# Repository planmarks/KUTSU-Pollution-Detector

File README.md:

<div align="center">

# KUTSU Sense

**Open environmental monitoring for the air you breathe.**

*CO₂ · VOC · NOx · combustible gas & smoke · temperature · humidity*

</div>

---

## What is KUTSU?

KUTSU is an environmental monitoring and awareness device. It watches indoor air for the
things you can't see or smell, shows the readings on a small OLED display, and **warns you
the moment conditions turn unhealthy** with an on-screen alarm, a buzzer and status LEDs.
Every reading is logged to a MicroSD card, and newer builds can stream data to a phone app or
feed a self-hosted dashboard (the KUTSU Hub) on a Raspberry Pi or spare PC. There's no cloud and no subscription.

KUTSU comes in three configurations:

| Configuration | For whom | Highlights |
|---|---|---|
| 🛠️ **Development platform** | Makers, researchers, civic & environmental projects | All buses and power broken out, fully open firmware |
| ✋ **Handheld** | On-site, walk-up spot checks | LiPo battery, compact, display-led UI, laser pointer |
| 🏠 **Stationary** | Long-term monitoring of rooms and large sites | 5 V powered, MQ-2 gas/smoke sensor, 5 V fan, Wi-Fi dashboard + multi-node mesh |

---

### Where to start

| I want to… | Go to |
|---|---|
| Understand or build the **current device** | [KUTSU 1.0](KUTSU%201.0/README.md) |
| Build a **handheld** from breakout modules | [KUTSU DIY → Handheld](KUTSU%20DIY/KUTSU%20Handheld/README.md) |
| Run the **site dashboard** for stationary units (Raspberry Pi / PC) | [KUTSU Hub](KUTSU%201.0/KutsuHub/README.md) |
| Build a **stationary node** from breakout modules (legacy) | [KUTSU DIY → Stationary](KUTSU%20DIY/KUTSU%20Stationary/README.md) |
| Hack on the original **CircuitPython** prototype | [KUTSU PICO](KUTSU%20PICO/README.md) |
| Read the **JSON data format** (Wi-Fi / SD) | [KUTSU 1.0 DATA_CONTRACT.md](KUTSU%201.0/KutsuFirmwareXIAOESP32Series/DATA_CONTRACT.md) (v4) · [Stationary](KUTSU%20DIY/KUTSU%20Stationary/Firmware/KutsuSense/DATA_CONTRACT.md) (v2) |

---

## Generations at a glance

| | **KUTSU PICO** | **KUTSU DIY — Handheld** | **KUTSU DIY — Stationary** | **KUTSU 1.0** |
|---|---|---|---|---|
| **Status** | Original prototype | Legacy, available | Legacy, available | ✅ **Current** |
| **MCU** | Pimoroni Pico LiPo (RP2040) | Seeed XIAO ESP32-C3 / C5 | Espressif ESP32-C5-DevKitC-1 v1.2 | Seeed XIAO ESP32-C6 / C5 / C3 / S3 |
| **Firmware** | CircuitPython 10.x | Arduino / C++ | Arduino / C++ | Arduino / C++ |
| **CO₂** | CCS811 (estimated eCO₂) | CCS811 (estimated eCO₂) | CCS811 (estimated eCO₂) | **SCD41 (true NDIR CO₂)**, CCS811 if fitted |
| **VOC** | SGP40 index · CCS811 TVOC | CCS811 TVOC | CCS811 TVOC | **SGP41 VOC index** |
| **NOx** | — | — | — | **SGP41 NOx index** |
| **Temp / RH** | HTU21D | HTU21D | HTU21D | **SHT40**, HTU21D if fitted |
| **Gas / smoke** | MQ-2 (raw) | — (5 V part, no budget) | MQ-2 (raw) | MQ-2 header (optional, raw) |
| **Feedback** | OLED · buzzer (SOS) | OLED · buzzer | OLED · buzzer · 3 LEDs | OLED · buzzer · warning LED |
| **Logging** | CSV → SD / flash | CSV → SD / flash | **JSON Lines** → SD / flash | **JSON Lines** → SD / flash |
| **Connectivity** | — | Passive Wi-Fi/BLE scanner | **BLE app link + Wi-Fi mesh dashboard** | Passive Wi-Fi/BLE scanner · BLE app link · **KUTSU Hub** (LAN dashboard on a Pi / PC) |
| **Extras** | NFC health tag | NFC health tag | NFC health tag | Laser marker · LiPo · power switch |

---

## How it works (all generations)

Every KUTSU build shares the same core design:

```text
            ┌──────────── once per second ────────────┐
 sensors ──▶ readSensors ─▶ history ─▶ evaluate ─▶ display / alarm ─▶ log row
            └──────────────────────────────────────────┘
                 buttons · buzzer · LEDs · radios run continuously in between
```

- **Sensing loop at 1 Hz.** Each sensor is read into a `Reading` struct. A missing or failed
  sensor is marked *invalid* and is never reported as a fake `0`.
- **Three severities.** Each metric is graded *good* / *warning* `!` / *alert* `!!`. Thresholds
  live in a single config file (`config.h` or `config.py`).
- **Alerts.** An alert brings up a pulsing full-screen warning (5 s on, 1 s gap) and a short
  buzzer pattern, plus LEDs where fitted. Press the screen button to dismiss it. It re-arms
  once the air recovers.
- **History.** The firmware keeps 60 one-minute averages per metric for the on-device
  one-hour charts.
- **Logging.** Data goes to the MicroSD card when one is present and falls back to internal
  flash otherwise. There is no RTC, so timestamps are uptime seconds until a phone or NTP
  supplies the time.

---

## Lineage

1. **KUTSU PICO.** The first prototype was a CircuitPython build on a Raspberry Pi Pico LiPo
   wired to Adafruit-style breakout modules.
2. **Move to ESP32.** CircuitPython does not support the ESP32-C5, so the firmware was
   rewritten in **Arduino/C++**. It then split into a **Handheld** build (XIAO, battery) and a
   **Stationary** build (DevKitC, 5 V, mesh dashboard).
3. **KUTSU 1.0.** The two branches merged onto **one board** and **one firmware**. It runs on
   any footprint-compatible XIAO (ESP32-C6, C5, C3 or S3). The sensors moved from CCS811 +
   HTU21D to the **Sensirion SCD41 / SGP41 / SHT40** stack, so CO₂ is now measured rather than
   estimated. The firmware detects what's fitted, so the old breakouts still work. Stationary
   units feed the KUTSU Hub, a dashboard and collector on a Raspberry Pi or PC.

---

## Roadmap

- [x] Sensirion SCD41 / SGP41 / SHT40 driver migration (KUTSU 1.0)
- [x] BLE app link + Wi-Fi mesh dashboard + JSON data contract (Stationary DIY build)
- [x] Port the JSON data contract to the KUTSU 1.0 firmware (XIAO C3/C5/C6/S3)
- [x] KUTSU Hub: LAN collector + dashboard (Raspberry Pi / Windows) for stationary units
- [x] NTP time source when on Wi-Fi (KUTSU 1.0)
- [ ] BLE app link on KUTSU 1.0 + companion app (React Native / Expo)
- [ ] On-site calibration of CO₂, VOC, NOx and MQ-2 thresholds

---

## ⚠️ Safety notice

KUTSU is an air-quality **awareness and monitoring** instrument. The MQ-2 reports a *relative*
combustible-gas and smoke level. **Do not rely on KUTSU as a certified smoke, carbon-monoxide
or life-safety alarm**, and never use it as the only safety device in a life-safety
application. For regulatory or safety-critical use, validate readings against reference
instruments on site.

---

## License

KUTSU Sense is released under the **[Apache License 2.0](LICENSE)**. This covers the firmware,
documentation and hardware design files (KiCad sources, Gerbers, 3D models). Third-party
libraries bundled in `KUTSU PICO/lib/` keep their own licenses.

---

<div align="center">

*KUTSU — "6th Sense" · By Papathought*

</div>

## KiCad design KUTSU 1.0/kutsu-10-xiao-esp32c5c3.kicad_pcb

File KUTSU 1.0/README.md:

# KUTSU 1.0

> **One board, every use case.** KUTSU 1.0 merges the earlier Handheld and Stationary
> prototypes into a single PCB: the **Kutsu 1 board (rev 3)**. It's built around a Seeed XIAO
> ESP32 module (**C3, C5, C6 or S3**, same footprint, one firmware) and a
> laboratory-calibrated Sensirion sensor stack.

[← Back to project overview](../README.md)

---

## 📚 Documentation

| Document | What's inside |
|---|---|
| **[HARDWARE.md](HARDWARE.md)** | Board overview, bill of materials, pin map, power, design files, fabrication |
| **[Firmware README](KutsuFirmwareXIAOESP32Series/README.md)** | Arduino IDE setup per XIAO module, libraries, wiring, stationary mode + hub, bring-up checklist |
| **[KUTSU Hub](KutsuHub/README.md)** | The LAN dashboard + data collector for stationary units. Runs on a Raspberry Pi or an old Windows PC |
| **[FIRMWARE.md](KutsuFirmwareXIAOESP32Series/FIRMWARE.md)** | Firmware internals: sensor detection, tasks, Wi-Fi state machine, UI, logging, known issues |
| **[DATA_CONTRACT.md](KutsuFirmwareXIAOESP32Series/DATA_CONTRACT.md)** | JSON-Lines record format used by the log, BLE and the KUTSU Hub |
| **[Kutsu Setup app](KutsuSetupApp/)** | Local desktop app to set up a device's WiFi over **Bluetooth or USB** — no nRF Connect needed |
| **[PROVISIONING.md](PROVISIONING.md)** | The BLE GATT + USB-serial setup contract the app and firmware share |
| [kutsu-project.md](kutsu-project.md) | Short product description |

---

## What it measures

| Reading | Sensor | Type | Units |
|---|---|---|---|
| **CO₂** | Sensirion **SCD41** | Photoacoustic NDIR (true CO₂) | ppm |
| **VOC index** | Sensirion **SGP41** | MOx gas sensor + Gas Index Algorithm | 1–500 |
| **NOx index** | Sensirion **SGP41** | MOx gas sensor + Gas Index Algorithm | 1–500 |
| **Temperature** | Sensirion **SHT40** | Digital T/RH | °C |
| **Humidity** | Sensirion **SHT40** | Digital T/RH | %RH |
| **Combustible gas / smoke** | **MQ-2** *(optional, external module)* | Analog MOx | relative |

The firmware **detects its sensors at boot** with an I²C scan, then shows and logs only what it
finds. The original DIY breakouts still work on the same firmware: **CCS811** (eCO₂ + TVOC) and
**HTU21D** (temp/RH). So does a plug-in **SSD1306 OLED module** in place of the on-board panel.

**Why the upgrade matters:** the earlier builds used a CCS811, which *estimates* CO₂ from VOCs.
The SCD41 **measures** CO₂ directly. The SGP41 adds separate **VOC and NOx** indices, which
give a much richer picture than a single "air quality" number.

---

## The three configurations

All three use the **same Kutsu 1 board**. What changes is which parts are fitted, how the
board is powered, and which firmware features are enabled.

| Configuration | Power | Distinctive parts | Networking |
|---|---|---|---|
| 🛠️ **Development platform** | USB-C 5 V | I²C, SD, MQ-2 and power broken out to pads | Open firmware, full access |
| ✋ **Handheld** | LiPo battery (USB-C charging) | Compact, display-led UI, laser marker, small fan | Stays off Wi-Fi. Data via SD card, BLE app or USB |
| 🏠 **Stationary** | 5 V mains / USB | Optional **MQ-2** module, **5 V fan** | Joins Wi-Fi and feeds the **[KUTSU Hub](KutsuHub/README.md)** dashboard on a Pi / PC |

One design to manufacture, one firmware codebase and one data format: a handheld unit and a
wall-mounted site unit speak the same language.

**Handheld vs. stationary is now a software mode**, not just a hardware build — switch it from
the [Kutsu Setup app](KutsuSetupApp/) (Bluetooth/USB), the mobile app or the serial console,
and it persists. In **handheld** mode the unit works stand-alone and stays off Wi-Fi. In
**stationary** mode it joins Wi-Fi, finds the **[KUTSU Hub](KutsuHub/README.md)** (a small app
on a Raspberry Pi or PC on the same network) and streams its readings and log there. The hub
keeps the history and serves the site dashboard. A fresh device boots in handheld mode. See
[PROVISIONING.md](PROVISIONING.md) for the full behavior model and the settings
(buzzer / LED / display / scanning / mode) a connected client can change.

---

## Quick start

1. Install the **esp32 by Espressif** core (≥ 3.3) and select your module: **XIAO_ESP32C3**,
   **XIAO_ESP32C5**, **XIAO_ESP32C6** or **XIAO_ESP32S3**.
2. On C3/C5/C6, set **Partition Scheme → Huge APP (3MB No OTA/1MB SPIFFS)**. Leave **USB CDC On
   Boot → Enabled** (the default); see the
   [firmware README](KutsuFirmwareXIAOESP32Series/README.md#1-board-setup-arduino-ide).
3. Install the libraries listed in the [firmware README](KutsuFirmwareXIAOESP32Series/README.md#2-libraries).
4. Open `KutsuFirmwareXIAOESP32Series/KutsuSense/KutsuSense.ino` and upload.
5. Open the Serial Monitor at **115200**. The I²C scan should list `0x3C 0x44 0x59 0x62`.
6. *(Optional, stationary use)* Start the **[KUTSU Hub](KutsuHub/README.md)** on a Pi or PC
   (`python3 kutsu_hub.py`). Then set the unit to **stationary** with Wi-Fi credentials, using
   the **[Kutsu Setup app](KutsuSetupApp/)** or the Serial Monitor (`mode stationary`,
   `ssid <network>`, `pass <password>`, `connect`). The unit finds the hub by itself. Open the
   address shown on the unit's **Hub** screen.

---

## On-device experience

- **Boot.** A splash screen ("KUTSU / 6th Sense / By Papathought") is followed by a self-test
  screen that shows OK/FAIL for each module.
- **Screens.** One button cycles through **Live → Stats (1-hour sparklines) → Wi-Fi networks →
  BLE devices → Hub** (hub address, sync state, Wi-Fi).
- **Alerts:**

  | Channel | Behaviour |
  |---|---|
  | 🖥️ Display | Full-screen WARNING that pulses (5 s on / 1 s gap) until you dismiss it |
  | 🔊 Buzzer | 3 short beeps once per alert; re-arms after the air recovers |
  | 💡 Warning LED | Solid on alert, slow blink on warning, off when clear |

- **Logging.** JSON Lines go to MicroSD (`/kutsu_log.jsonl`), with internal flash as the
  fallback. Format: [DATA_CONTRACT.md](KutsuFirmwareXIAOESP32Series/DATA_CONTRACT.md).
- **KUTSU Hub.** In stationary mode the unit streams to the hub on the LAN, which charts
  every unit's history, raises alerts and exports CSV.
- **Laser marker.** A hardware switch lights a laser so you can point at the spot you're sampling.

### Default thresholds

| Metric | Warning `!` | Alert `!!` |
|---|---|---|
| CO₂ (SCD41) | ≥ 1000 ppm | ≥ 2000 ppm |
| eCO₂ / TVOC (CCS811 breakout) | ≥ 900 ppm / ≥ 660 ppb | ≥ 2000 ppm / ≥ 3000 ppb |
| VOC index | ≥ 250 | ≥ 400 |
| NOx index | ≥ 20 | ≥ 150 |
| Temperature | 50–60 °C | < 0 °C or > 60 °C |
| Humidity | 25–30 % or 60–70 %RH | < 25 % or > 70 %RH |

> [!NOTE]
> The CO₂, VOC and NOx limits are **provisional**. Calibrate them on site. You can change any
> of them in `config.h`.

---

## Directory contents

| Path | Contents |
|---|---|
| `kutsu-10-xiao-esp32c5c3.kicad_pro` / `.kicad_sch` / `.kicad_pcb` | KiCad project: **Kutsu 1, rev 3** |
| `kutsu-10-xiao-esp32c5c6.net` | Exported netlist *(older, rev 2; see [HARDWARE.md](HARDWARE.md#design-files))* |
| `KUTSUV1 Gerber/` + `KUTSUV1 Gerber.zip` | Fabrication gerbers + drill files |
| `3D/` | PCB render, board models (`.stl`, `.glb`) |
| `Case/` | Enclosure model (`Kutsu 1 Case.blend`) + render |
| `Kutsu Handheld 3D Model.blend` | Industrial-design model |
| `KutsuFirmwareXIAOESP32Series/` | Firmware for this board (XIAO ESP32-C3 / C5 / C6 / S3) |
| `KutsuHub/` | KUTSU Hub: LAN collector + dashboard for stationary units (Python, Raspberry Pi / Windows) |
| `BOM/` | Bill of materials / compliance sheet + component datasheets |
| `*.kicad_prl`, `fp-info-cache`, `.history/` | KiCad local/editor state, not part of the design |

---

## Other hardware variants

The XIAO footprint is pin-identical across the C3, C5, C6 and S3, and this board's firmware
supports all four. The earlier boards and their firmware are still available:

| Variant | MCU | Sensors | Where |
|---|---|---|---|
| **KUTSU 1.0** *(this)* | XIAO ESP32-C3 / C5 / C6 / S3 | SCD41 · SGP41 · SHT40 (+ CCS811 · HTU21D · MQ-2 if fitted) | [`KutsuFirmwareXIAOESP32Series`](KutsuFirmwareXIAOESP32Series/) |
| DIY Handheld | XIAO ESP32-C3 / C5 | CCS811 · HTU21D · | [`KUTSU DIY/KUTSU Handheld`](../KUTSU%20DIY/KUTSU%20Handheld/README.md) |
| DIY Stationary | ESP32-C5-DevKitC-1 | CCS811 · HTU21D · MQ-2 · 3 LEDs | [`KUTSU DIY/KUTSU Stationary`](../KUTSU%20DIY/KUTSU%20Stationary/README.md) |

---

## Roadmap

- [x] Sensirion SCD41 / SGP41 / SHT40 driver migration
- [x] One firmware for XIAO ESP32-C3 / C5 / C6 / S3
- [x] Boot-time I²C detection: on-board Sensirion stack, DIY CCS811/HTU21D breakouts, OLED panel or module
- [x] JSON data contract, ported from the
      [Stationary firmware](../KUTSU%20DIY/KUTSU%20Stationary/Firmware/KutsuSense/README.md)
- [x] **[KUTSU Hub](KutsuHub/README.md)**: LAN collector + dashboard on a Raspberry Pi / PC. It
      replaces the ESP32-hosted dashboard and mesh election, with gap-free history after outages
- [ ] Hub → device settings (thresholds, names) from the dashboard
- [x] NTP time sync when online
- [x] BLE GATT provisioning service + **[Kutsu Setup app](KutsuSetupApp/)** (Bluetooth **or** USB
      WiFi setup from the desktop) — see [PROVISIONING.md](PROVISIONING.md)
- [ ] Hardware bring-up of the merged firmware on each XIAO module (incl. BLE server+scanner coexistence)
- [ ] Package Kutsu Setup as an installable Tauri/Electron app; add firmware info/OTA, FRC calibration, node naming
- [ ] Mobile companion app (React Native / Expo) on the same GATT contract
- [ ] SCD41 fresh-air forced-recalibration (FRC) workflow; on-site threshold tuning
- [ ] BLE bonding / pairing PIN before deploying where open provisioning isn't acceptable

---

## For industrial & site deployment

- **Calibrated measurements.** True CO₂ (NDIR), VOC and NOx indices, temperature and humidity
  come from Sensirion sensors, not estimated proxies.
- **Standalone or fleet.** Each node works on its own: display, LED, alarm and SD log. Put
  several on one Wi-Fi network with the KUTSU Hub running on a Raspberry Pi or spare PC, and
  you get a live site dashboard with full history. There's no cloud and nothing to install
  beyond Python.
- **Your data stays yours.** Logs go to a removable MicroSD card in an open format. There's no
  cloud, no account and no per-seat fee.
- **Resilient.** Every node logs locally whatever the network state, and a failed sensor is
  marked invalid rather than reported as zero.
- **Flexible power.** Run it from 5 V mains with an active fan for permanent installs, or from a
  battery for portable audits.

> [!WARNING]
> KUTSU is an air-quality **awareness** instrument. The MQ-2 reports a *relative* gas/smoke
> level. Do not rely on it as a certified smoke, CO or life-safety alarm.

---

*By Papathought.*

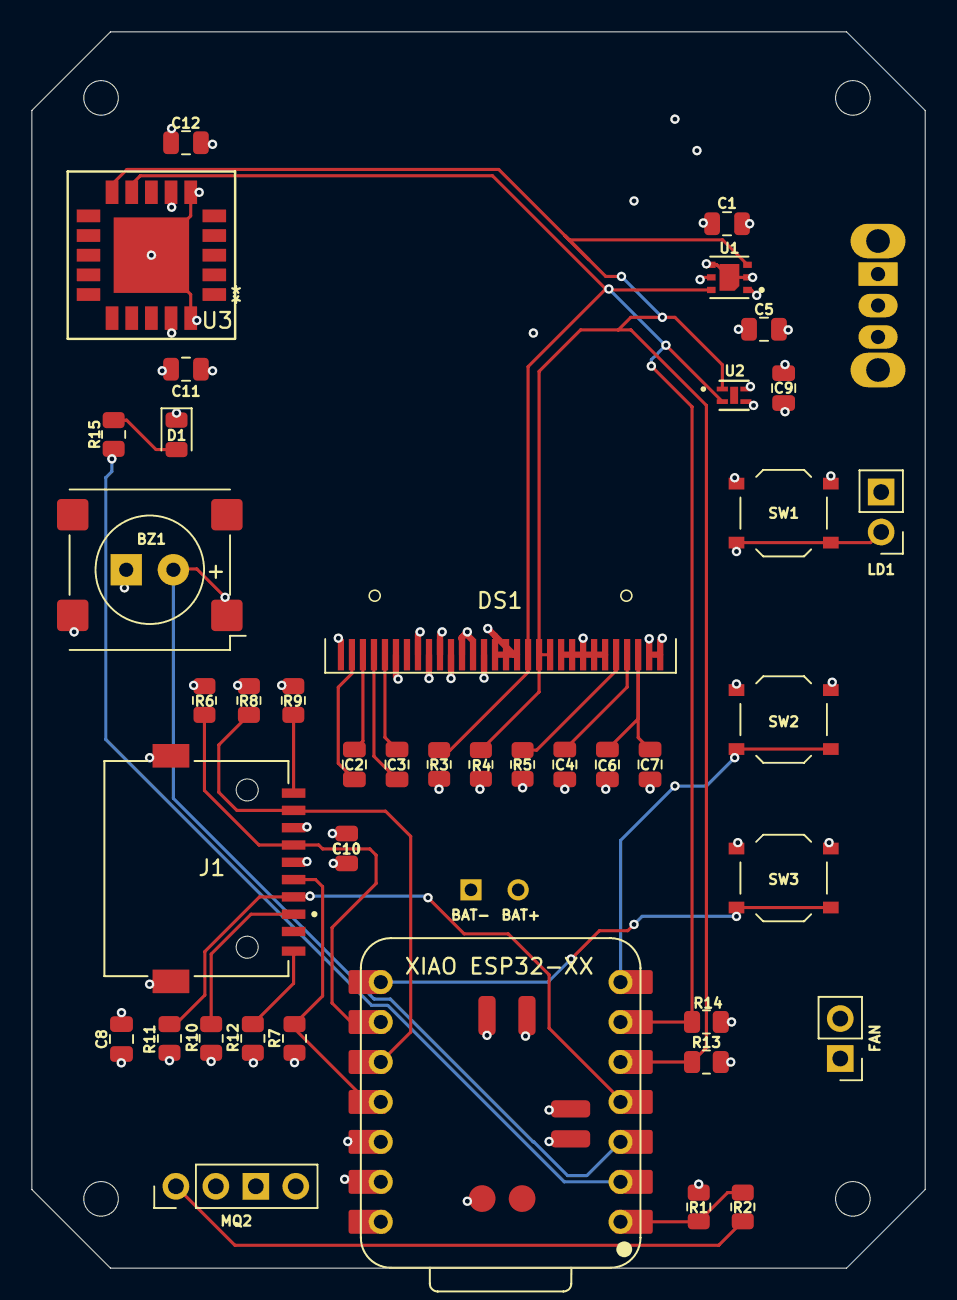
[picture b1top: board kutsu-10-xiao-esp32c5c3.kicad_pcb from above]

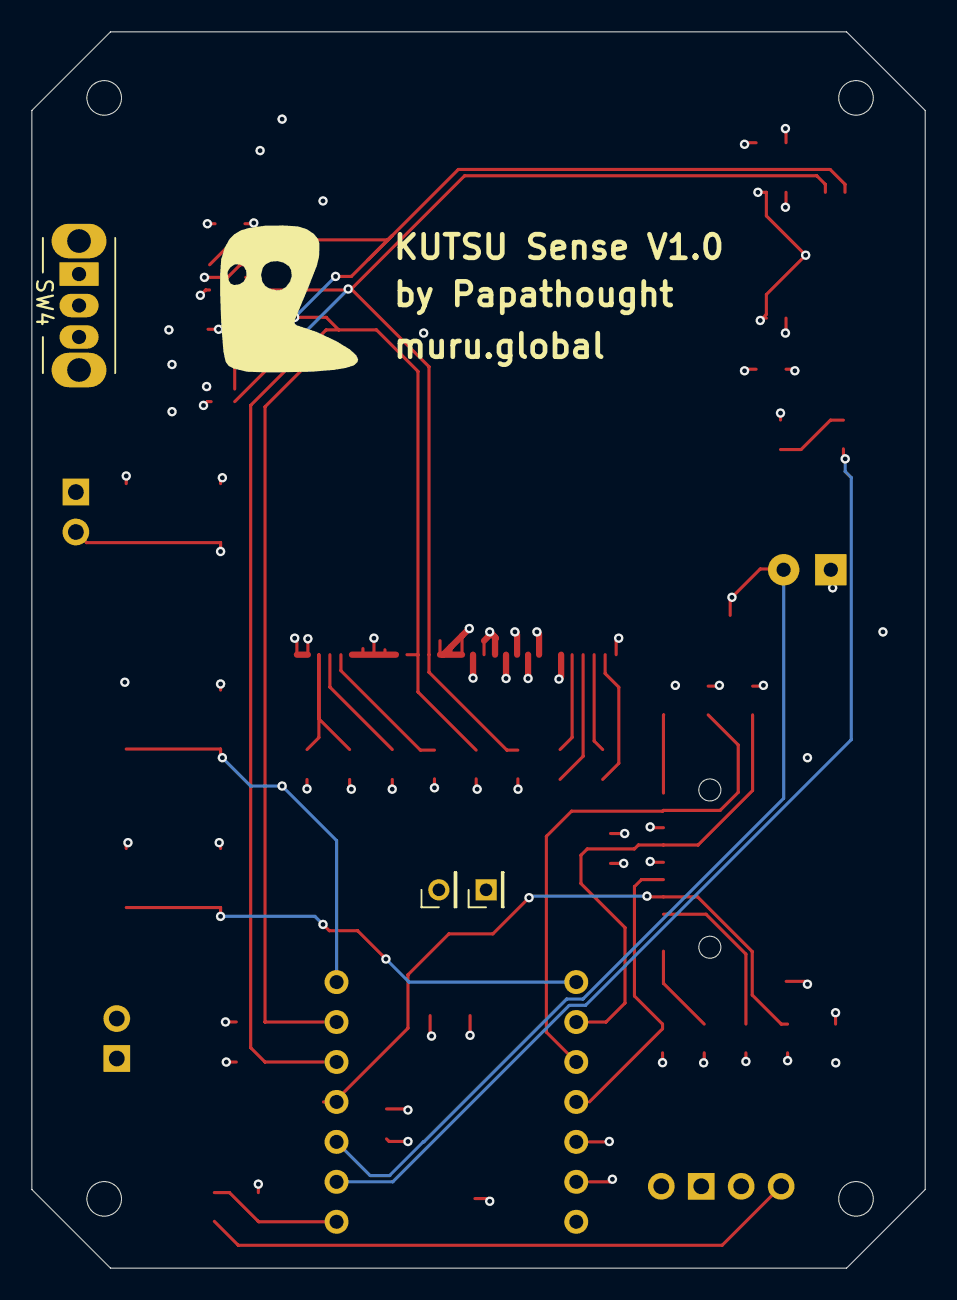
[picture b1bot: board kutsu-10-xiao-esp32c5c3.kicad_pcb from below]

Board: 4 copper layers, 56.8 x 78.6 mm, 45 parts (3 on the bottom side), 28 nets.

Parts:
BAT+: PinHeader_1x01_P2.00mm_Vertical
BAT-: PinHeader_1x01_P2.00mm_Vertical
BZ1: Buzzer; MagneticBuzzer_PUI_SMT-1028-T-2-R
BZ1#2: MagneticBuzzer_Kobitone_254-EMB73-RO
C1, C5, C6, C9, C10, C11, C12: 0.1uF; C_0805_2012Metric
C2, C3: 2.2 µF; C_0805_2012Metric
C4: 1uF; C_0805_2012Metric
C7: 2uF; C_0805_2012Metric
C8: 10uF; C_0805_2012Metric
D1: LED; LED_0805_2012Metric
DS1: OLED-128O064D
FAN: PinHeader_1x02_P2.54mm_Vertical
J1: MSD-11-A; CUI_MSD-11-A
LD1: D_Laser_1A3C; PinHeader_1x02_P2.54mm_Vertical
MQ2: PinHeader_1x04_P2.54mm_Vertical
R1: 20K; R_0805_2012Metric
R2: 10K; R_0805_2012Metric
R3, R4, R6, R7, R8, R9, R10, R11, R12, R13, R14, R15: 4.7K; R_0805_2012Metric
R5: 390K; R_0805_2012Metric
SW1, SW2, SW3: SW_Push; SW_Push_1P1T_XKB_TS-1187A
SW4: SW_SPDT; SW_Slide_SPDT_Angled_CK_OS102011MA1Q
U1: SGP41-D-R4; XDCR_SGP41-D-R4
U2: SHT40-AD1B-R3; DFN4_SHT4x_SEN
U3: SCD41-D-R2; QFN20_SCD41-D-R2_SEN
XIAO ESP32: XIAO-ESP32-C5-DIP

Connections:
5V: FAN.2, MQ2.4, XIAO ESP32.14
+3V3: C1.2, C5.1, C8.1, C9.1, C10.1, C11.1, C12.2, DS1.6 (VBAT), DS1.9 (VDD), DS1.11 (BS1), DS1.14 (~RES), J1.P4 (VDD), R3.1, R4.1, R6.2, R7.2, R8.2, R9.2, R10.2, R11.2, R12.2, R13.1, R14.1, SW1.2, U1.1 (VDD), U1.5 (VDDH), U2.3 (VDD), U3.7 (VDD), U3.19 (VDDH), XIAO ESP32.12
AO: MQ2.1, R2.2
BTN1: SW2.1, XIAO ESP32.7
BTN2: SW3.2, XIAO ESP32.8
BTSW1: BAT+.1, SW4.2 (B)
D1: R15.2, XIAO ESP32.2
GND: BZ1.2 (-), BZ1#2.2, C1.1, C4.2, C5.2, C6.2, C7.2, C8.2, C9.2, C10.2, C11.2, C12.1, D1.1 (K), DS1.1 (GND), DS1.8 (VSS), DS1.10 (BS0), DS1.12 (BS2), DS1.13 (~CS), DS1.15 (D/~C), DS1.16 (R/~W), DS1.17 (E/~RD), DS1.21 (D3), DS1.22 (D4), DS1.23 (D5), DS1.24 (D6), DS1.25 (D7), DS1.29 (VLSS), DS1.30 (GND), FAN.1, J1.G1 (COVER_GND), J1.G2 (COVER_GND), J1.P6 (VSS), LD1.2, MQ2.3, R1.1, R5.1, SW2.2, SW3.1, U1.2 (VSS), U1.4 (GND), U1.7 (GND), U2.4 (VSS), U3.6 (GND), U3.20 (GND), U3.21 (EPAD), XIAO ESP32.13
GPIO4: BZ1.1 (+), BZ1#2.1, XIAO ESP32.3
MQ2AO: R1.2, R2.1, XIAO ESP32.1
unnamed: D1.2 (A), R15.1
unnamed: C3.2, DS1.5 (C1N)
unnamed: C3.1, DS1.4 (C1P)
unnamed: C2.2, DS1.2 (C2N)
unnamed: C2.1, DS1.3 (C2P)
unnamed: DS1.26 (IREF), R5.2
unnamed: C6.1, C7.1, DS1.28 (VCC)
unnamed: C4.1, DS1.27 (VCOMH)
unnamed: J1.P8 (DAT1), R9.1
unnamed: J1.P1 (DAT2), R10.1
unnamed: J1.CD, R12.1
unnamed: LD1.1 (A_1), SW1.1
SCL: DS1.18 (D0), R3.2, R14.2, U1.6 (SCL), U2.2 (SCL), U3.9 (SCL), XIAO ESP32.6
SDA: DS1.19 (D1), DS1.20 (D2), R4.2, R13.2, U1.3 (SDA), U2.1 (SDA), U3.10 (SDA), XIAO ESP32.5
SDCLK: J1.P5 (CLK), R6.1, XIAO ESP32.9
SDCS: J1.P2 (CD/DAT3), R11.1, XIAO ESP32.4
SDSI: J1.P3 (CMD), R7.1, XIAO ESP32.11
SDSO: J1.P7 (DAT0), R8.1, XIAO ESP32.10

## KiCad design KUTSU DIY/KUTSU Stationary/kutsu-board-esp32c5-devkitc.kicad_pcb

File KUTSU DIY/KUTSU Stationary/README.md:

# KUTSU Stationary

> The **fixed-install** KUTSU: a 5 V-powered air monitor that sits in a room and watches it
> continuously. Several units link into a self-hosted **Wi-Fi mesh with a web dashboard**, so
> every room is visible from one page.

[← KUTSU DIY](../README.md) · [Project overview](../../README.md)

---

## 📚 Documentation

| Document | What's inside |
|---|---|
| **[HARDWARE.md](HARDWARE.md)** | Board v0.3S, bill of materials, pin map, power, fabrication files |
| **[Firmware/README.md](Firmware/README.md)** | Firmware overview and how to flash the ESP32-C5 |
| [KutsuSense/README.md](Firmware/KutsuSense/README.md) | Arduino setup, flashing troubleshooting, libraries, bring-up |
| [KutsuSense/FIRMWARE.md](Firmware/KutsuSense/FIRMWARE.md) | Firmware internals: LEDs, UI, logging, BLE, mesh, dashboard |
| [KutsuSense/WIRING.md](Firmware/KutsuSense/WIRING.md) | Full wiring table, pin rationale, Mermaid wiring diagram |
| [KutsuSense/DATA_CONTRACT.md](Firmware/KutsuSense/DATA_CONTRACT.md) | JSON record schema (v2) shared by SD, BLE and Wi-Fi |
| [idf-flashtest/README.md](Firmware/idf-flashtest/README.md) | ESP-IDF LED-blink test for checking the toolchain |

---

## At a glance

| | |
|---|---|
| **MCU** | Espressif **ESP32-C5-DevKitC-1 v1.2** (on-board PCB antenna, more exposed GPIO than a XIAO) |
| **Power** | **5 V** mains adapter or USB |
| **Sensors** | **CCS811** (eCO₂ / TVOC) · **HTU21D** (temperature / humidity) · **MQ-2** (combustible gas / smoke) |
| **Feedback** | OLED · buzzer · **three status LEDs** 🟢 🟡 🔴 |
| **Display** | **Optional:** the LEDs carry the status, so the unit can run headless |
| **Fan** | 5 V fan for proper room-air circulation |
| **Storage** | **JSON Lines** on MicroSD, flash fallback |
| **Connectivity** | **BLE app link** + **Wi-Fi master/slave mesh** + **web dashboard** |

---

## Status LEDs

| LEDs | Meaning |
|---|---|
| 🟢 Green solid | All good |
| 🟢 + 🟡 Green + yellow solid | A warning on up to 3 metrics |
| 🟡 Yellow solid (green off) | Warnings on **more than 3** metrics: conditions are sub-optimal |
| 🔴 Red blinking | **Alert.** Shown together with the OLED alarm and the buzzer |
| 🟡 Yellow blinking | A required sensor failed to start |

At power-on the LEDs blink green → yellow → red as a self-test. If several states apply at
once, the priority is **Alert > Error > Warning > Good**.

---

## Web dashboard and node mesh

```mermaid
flowchart LR
    Phone[📱 Phone app] -- BLE: Wi-Fi creds, time, location --> A
    A[Kutsu-A1B2C3<br/>MASTER] -- serves --> Browser[💻 http://kutsu-a1b2c3.local/]
    B[Kutsu-D4E5F6<br/>SLAVE] -- POST /api/ingest --> A
    C[Kutsu-778899<br/>SLAVE] -- POST /api/ingest --> A
    Browser -- poll /api/nodes every 2 s --> A
```

1. **Provision over BLE.** The phone app writes the Wi-Fi SSID, password and room name, and
   the node stores them in NVS.
2. **The first node on the network becomes MASTER.** It finds no peer over mDNS
   (`_kutsu._tcp`), so it starts the web dashboard at `http://kutsu-<id>.local/`.
3. **Each later node becomes a SLAVE** and POSTs every sample to the master.
4. **The dashboard** shows one card per room, coloured by severity, with per-node drill-down.
5. **The mesh heals itself.** Election clashes resolve to the lower MAC, and a slave that
   loses its master re-elects.

Every node keeps its own durable log on SD regardless of role. **There's no cloud, no account
and no subscription.**

---

## Thresholds

| Shown as | Sensor | Unit | Warning `!` | Alert |
|---|---|---|---|---|
| `eCO2` | CCS811 | ppm | ≥ 900 | ≥ 2000 |
| `TVOC` | CCS811 | ppb | ≥ 660 | ≥ 3000 |
| `Temp` | HTU21D | °C | 50–60 | < 0 or > 60 |
| `Hum` | HTU21D | %RH | 25–30 / 60–70 | < 25 or > 70 |
| `Gas` | MQ-2 | raw 0–4095 | ≥ 1800 | ≥ 2600 |

> [!IMPORTANT]
> The MQ-2 reading is a **raw relative level**, not calibrated ppm. Tune `GAS_WARN` and
> `GAS_HARM` in `config.h` against a real smoke test. KUTSU is not a certified smoke or
> life-safety alarm.

---

## How it differs from the Handheld

| | Stationary | Handheld |
|---|---|---|
| Status LEDs / headless | ✅ | — |
| MQ-2 gas sensor | ✅ (5 V available) | — |
| Web dashboard + mesh | ✅ | — |
| BLE app link | ✅ | Planned |
| Log format | JSON Lines | CSV |
| Wi-Fi/BLE scan screens | Removed | ✅ |

---

## Notes and open items

- **CCS811 run-in.** Readings of ~400 ppm eCO₂ and near-0 TVOC at rest are normal. The
  baseline needs ~20 min run-in and ~48 h burn-in.
- **No RTC.** Timestamps are uptime seconds until a phone syncs the clock over BLE. After that
  they're real epoch time.
- **Strapping pins.** The red LED is on GPIO0 and the yellow LED on GPIO26. Both are safe as
  weak outputs, but check your board revision. See [WIRING.md](Firmware/KutsuSense/WIRING.md).
- **Flashing the C5 is fiddly** with the Arduino-bundled esptool. See the
  [troubleshooting guide](Firmware/KutsuSense/README.md#1-board-setup-arduino-ide--esp32-c5-devkitc-1-v12).

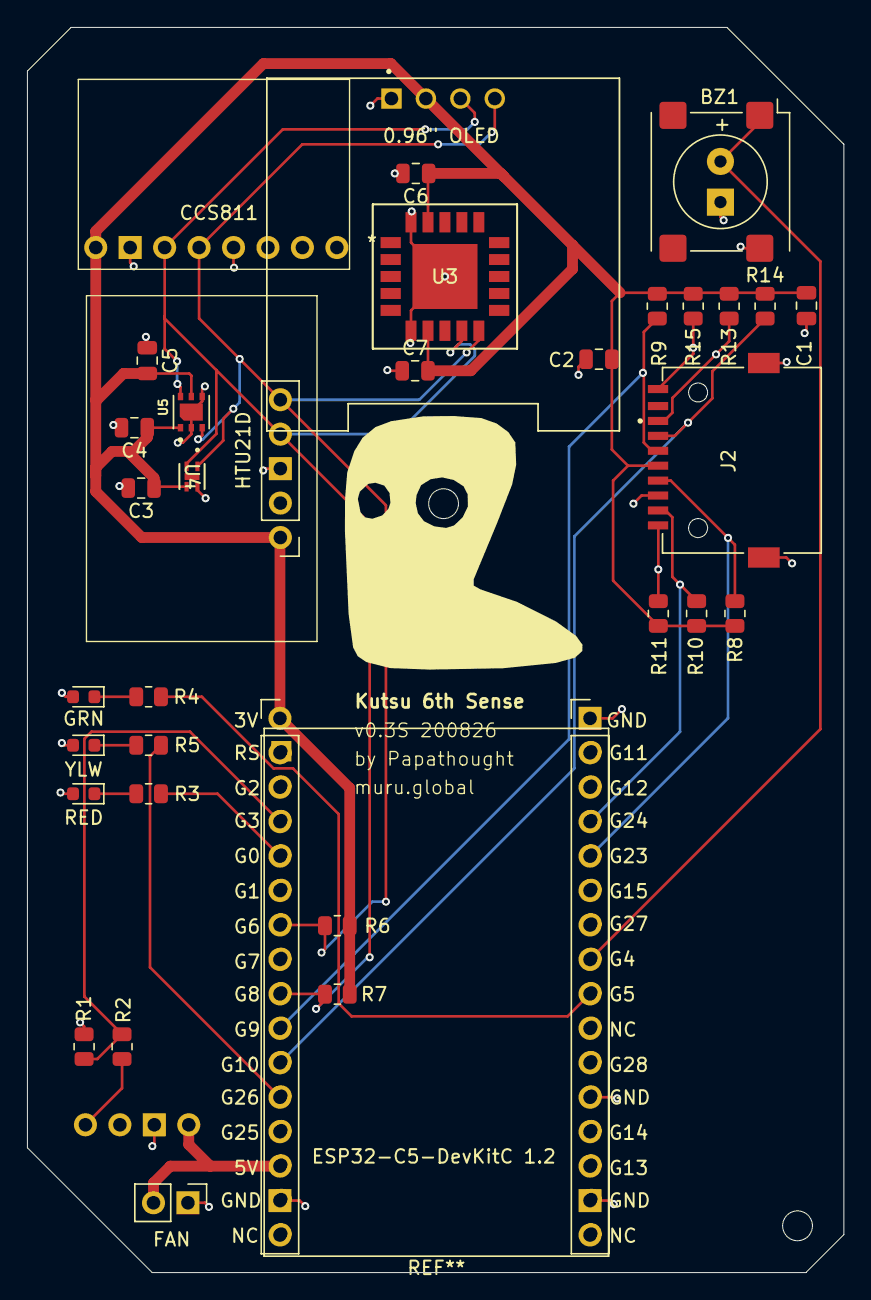
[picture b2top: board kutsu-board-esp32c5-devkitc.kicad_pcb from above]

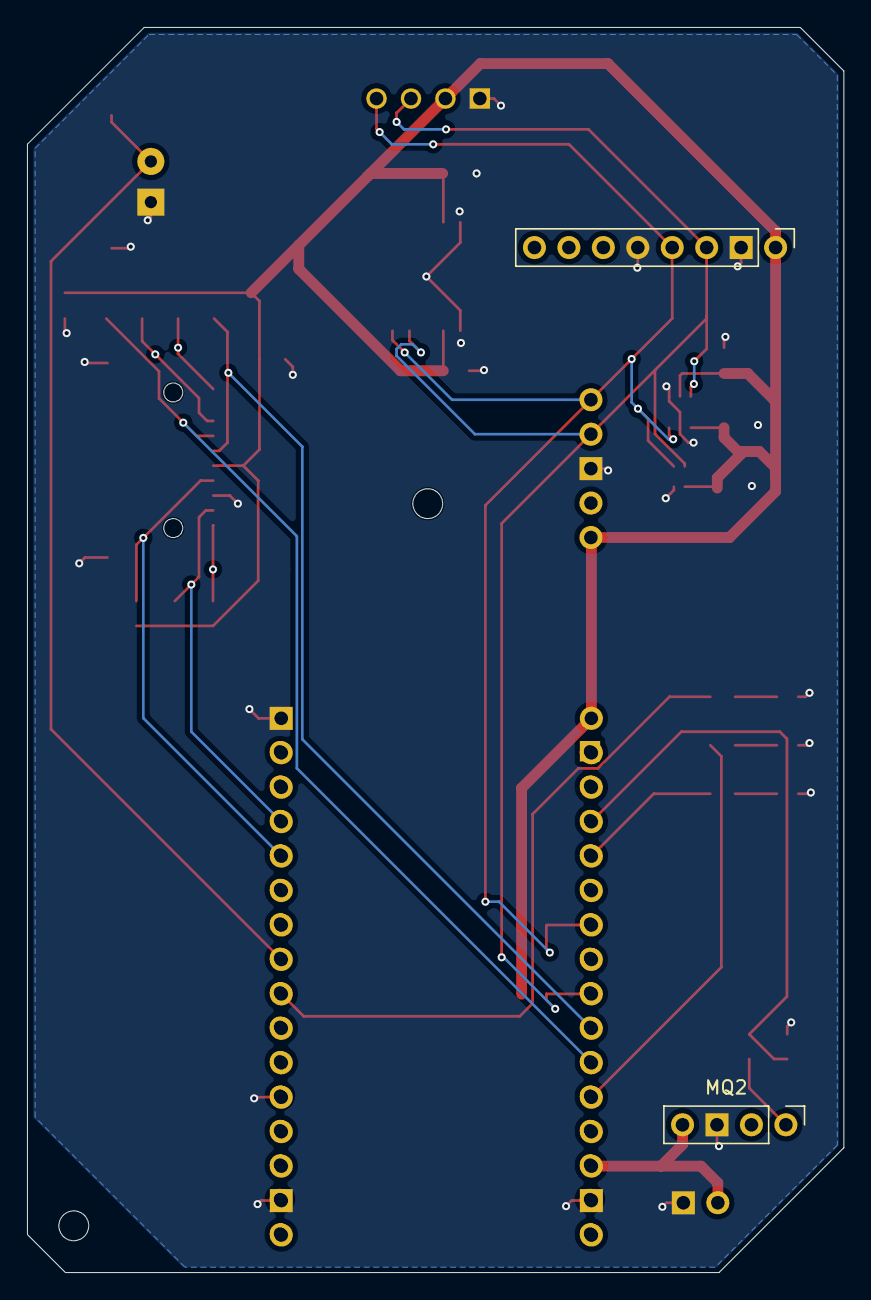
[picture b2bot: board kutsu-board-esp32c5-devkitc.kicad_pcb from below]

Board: 2 copper layers, 60.2 x 91.8 mm, 34 parts (2 on the bottom side), 17 nets.

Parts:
0.96" OLED: DM-OLED096-636; MODULE_DM-OLED096-636
BZ1: Buzzer; MagneticBuzzer_PUI_SMT-1028-T-2-R
C1: 10uF; C_0805_2012Metric
C2, C3, C4, C5, C6, C7: 0.1uF; C_0805_2012Metric
CCS811: PinHeader_1x08_P2.54mm_Vertical
FAN: PinHeader_1x02_P2.54mm_Vertical
GRN: LED_0603_1608Metric
HTU21D: PinHeader_1x05_P2.54mm_Vertical
J2: MSD-11-A; CUI_MSD-11-A
MQ2: PinHeader_1x04_P2.54mm_Vertical
R1: 20K; R_0805_2012Metric
R2: 10K; R_0805_2012Metric
R3, R4, R5, R6, R7, R8, R9, R10, R11, R13, R14, R15: 4.7K; R_0805_2012Metric
RED: LED_0603_1608Metric
U3: SCD41-D-R2; QFN20_SCD41-D-R2_SEN
U4: SHT40-AD1B-R3; DFN4_SHT4x_SEN
U5: SGP41-D-R4; XDCR_SGP41-D-R4
YLW: LED_0603_1608Metric

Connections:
5V: FAN.2, MQ2.4
+3V3: 0.96" OLED.2 (VCC_IN), C1.1, C2.1, C3.1, C4.1, C5.2, C6.1, C7.2, CCS811.1, HTU21D.1, J2.P4 (VDD), R6.1, R7.1, R8.2, R9.2, R10.2, R11.2, R13.2, R14.2, R15.2, U3.7 (VDD), U3.19 (VDDH), U4.3 (VDD), U5.1 (VDD), U5.5 (VDDH)
AO: MQ2.1, R2.2
GND: 0.96" OLED.1 (GND), BZ1.2 (-), C1.2, C2.2, C3.2, C4.2, C5.1, C6.2, C7.1, CCS811.2, CCS811.5, FAN.1, GRN.2, HTU21D.3, J2.G1 (COVER_GND), J2.G2 (COVER_GND), J2.P6 (VSS), MQ2.3, R1.1, RED.2, U3.6 (GND), U3.20 (GND), U3.21 (EPAD), U4.4 (VSS), U5.2 (VSS), U5.4 (GND), U5.7 (GND), YLW.2
MQ2AO: R1.2, R2.1
unnamed: R3.1, RED.1
unnamed: GRN.1, R4.1
unnamed: R5.1, YLW.1
unnamed: J2.P8 (DAT1), R11.1
unnamed: J2.P1 (DAT2), R13.1
unnamed: J2.CD, R15.1
SCL: 0.96" OLED.3 (SCL), CCS811.3, HTU21D.4, R7.2, U3.9 (SCL), U4.2 (SCL), U5.6 (SCL)
SDA: 0.96" OLED.4 (SDA), CCS811.4, HTU21D.5, R6.2, U3.10 (SDA), U4.1 (SDA), U5.3 (SDA)
SDCLK: J2.P5 (CLK), R8.1
SDCS: J2.P2 (CD/DAT3), R14.1
SDSI: J2.P3 (CMD), R9.1
SDSO: J2.P7 (DAT0), R10.1

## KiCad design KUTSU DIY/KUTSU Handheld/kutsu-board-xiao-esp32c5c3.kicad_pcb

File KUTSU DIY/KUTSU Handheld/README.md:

# KUTSU Handheld

> The **portable** KUTSU: a battery-powered, take-it-with-you air monitor. It reads eCO₂, TVOC,
> temperature and humidity, shows them on an OLED and sounds an alarm when conditions turn
> dangerous.

[← KUTSU DIY](../README.md) · [Project overview](../../README.md)

---

## 📚 Documentation

| Document | What's inside |
|---|---|
| **[HARDWARE.md](HARDWARE.md)** | Board v0.4P, bill of materials, wiring, power, fabrication files |
| **[Firmware/README.md](Firmware/README.md)** | Choosing between the XIAO ESP32-C3 and ESP32-C5 firmware |
| [C3 firmware setup](Firmware/KutsuFirmwareXIAOESP32C3/README.md) · [C3 internals](Firmware/KutsuFirmwareXIAOESP32C3/FIRMWARE.md) | XIAO ESP32-C3 (2.4 GHz) build |
| [C5 firmware setup](Firmware/KutsuFirmwareXIAOESP32C5/README.md) · [C5 internals](Firmware/KutsuFirmwareXIAOESP32C5/FIRMWARE.md) | XIAO ESP32-C5 (2.4 + 5 GHz) build |

---

## At a glance

| | |
|---|---|
| **MCU** | Seeed **XIAO ESP32-C5** or pin-compatible **XIAO ESP32-C3** |
| **Power** | Rechargeable **LiPo**, charged over the XIAO's USB-C |
| **Sensors** | **CCS811** (eCO₂ / TVOC) · **HTU21D** (temperature / humidity) |
| **Feedback** | 0.96" 128 × 64 OLED + active buzzer. The display is the primary interface |
| **Storage** | MicroSD (CSV), internal flash as fallback |
| **Extras** | Laser pointer · small 3 V fan |
| **Radios** | Passive Wi-Fi and BLE scanners on dedicated screens |

### Design choices

- **No MQ-2.** The MQ-2 is a 5 V part with a heater that draws ~150 mA, which the battery
  budget can't support. Air quality comes from the CCS811 only. The Stationary variant keeps
  the MQ-2.
- **Small fan.** You hold the handheld at a spot for a reading, so it only needs light airflow.
  Sustained room circulation is the Stationary unit's job.
- **Display-led UI.** The OLED and buzzer convey everything. There are no traffic-light LEDs
  and no on-board web server.

---

## Using it

1. **Power on.** A welcome screen ("KUTSU / 6th Sense / By Papathought") appears, then a
   boot-status screen showing OK or FAIL for each module.
2. **Read the live screen:** eCO₂, TVOC, Temp and Hum. A `!` marks a warning.
3. **Press the screen button** to cycle **Live → Stats (one-hour chart) → Wi-Fi networks →
   BLE devices → Live**.
4. **Alarm.** When any metric hits alert level, a full-screen WARNING pulses and the buzzer
   beeps 3 times. Press the button to dismiss it.
5. **Pull the SD card** to read `/kutsu_log.csv`, plus `/kutsu_net.csv` and `/kutsu_dev.csv`
   for the scan snapshots.

### Thresholds

| Shown as | Sensor | Unit | Warning `!` | Alert |
|---|---|---|---|---|
| `eCO2` | CCS811 | ppm | ≥ 900 | ≥ 2000 |
| `TVOC` | CCS811 | ppb | ≥ 660 | ≥ 3000 |
| `Temp` | HTU21D | °C | 50–60 | < 0 or > 60 |
| `Hum` | HTU21D | %RH | 25–30 / 60–70 | < 25 or > 70 |

---

## How it differs from the Stationary unit

| | Handheld | Stationary |
|---|---|---|
| Status LEDs | — | Green / yellow / red; can run headless |
| MQ-2 gas | — | ✅ |
| Web dashboard / mesh | — (BLE companion app planned) | ✅ |
| Log format | CSV | JSON Lines |
| Wi-Fi/BLE scan screens | ✅ | Removed in favour of outbound connectivity |

---

## Notes and open items

- **CCS811 run-in.** Readings of ~400 ppm eCO₂ and near-0 TVOC at rest are normal. The
  baseline needs ~20 min run-in and ~48 h burn-in.
- **No RTC.** Log timestamps are uptime seconds.
- **ESP32-C3 strapping pins.** D8 and D9 (SD SCK/MISO) are boot-strapping pins on the C3. If
  the board won't boot with a card inserted, reset it with the card removed.
- **Roadmap.** A BLE link to a companion app using the shared
  [JSON data contract](../KUTSU%20Stationary/Firmware/KutsuSense/DATA_CONTRACT.md).

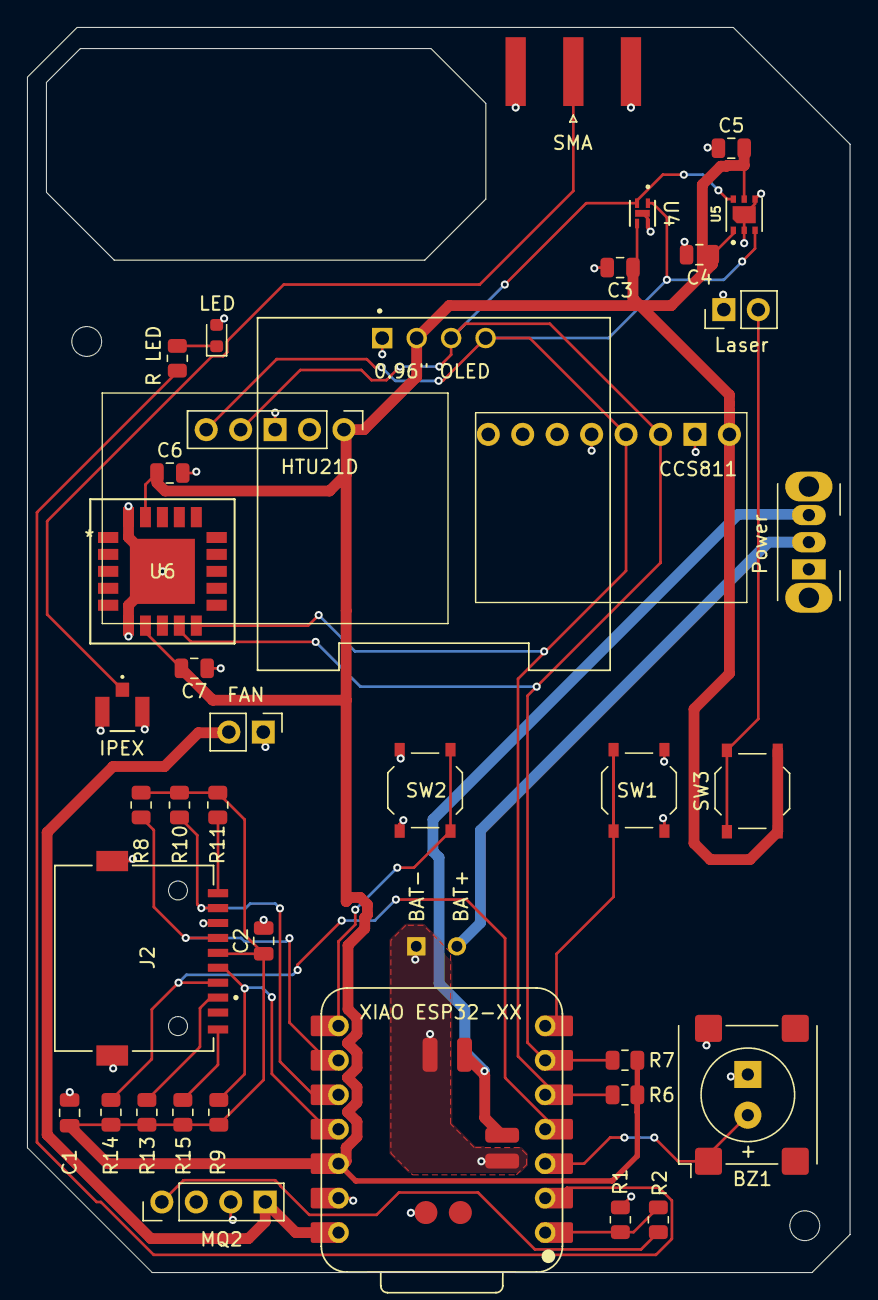
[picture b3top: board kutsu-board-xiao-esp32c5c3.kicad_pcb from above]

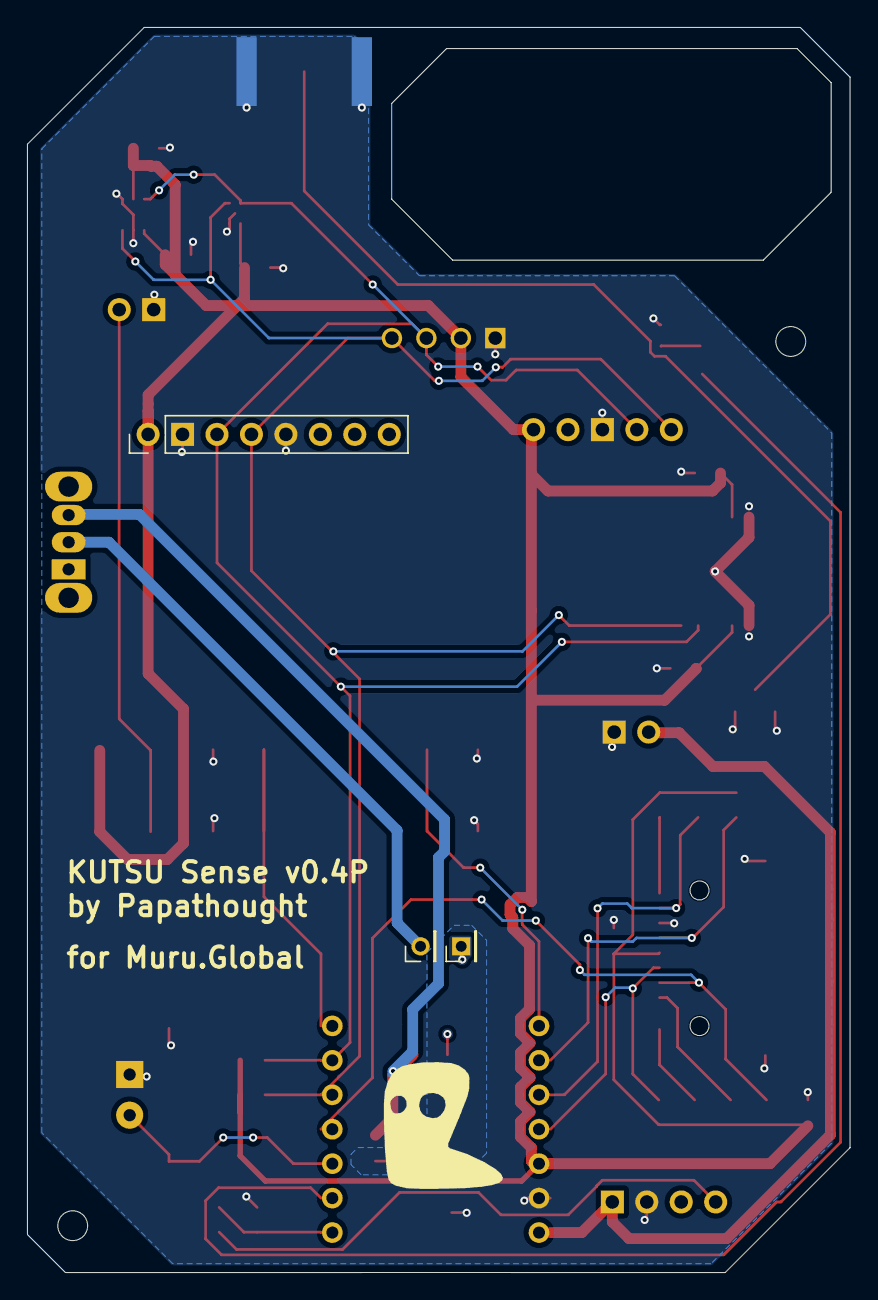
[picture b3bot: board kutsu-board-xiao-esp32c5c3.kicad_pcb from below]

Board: 2 copper layers, 60.7 x 91.8 mm, 41 parts (3 on the bottom side), 22 nets.

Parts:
0.96" OLED: DM-OLED096-636; MODULE_DM-OLED096-636
BAT+: PinHeader_1x01_P2.00mm_Vertical
BAT-: PinHeader_1x01_P2.00mm_Vertical
BZ1: Buzzer; MagneticBuzzer_PUI_SMT-1028-T-2-R
BZ1#2: MagneticBuzzer_Kobitone_254-EMB73-RO
C1: 10uF; C_0805_2012Metric
C2, C3, C4, C5, C6, C7: 0.1uF; C_0805_2012Metric
CCS811: PinHeader_1x08_P2.54mm_Vertical
FAN: PinHeader_1x02_P2.54mm_Vertical
HTU21D: PinHeader_1x05_P2.54mm_Vertical
IPEX: MHF_I_RECE_IPX; MHF I_RECE_IPX
J2: MSD-11-A; CUI_MSD-11-A
LED: LED_0603_1608Metric
Laser: PinHeader_1x02_P2.54mm_Vertical
MQ2: PinHeader_1x04_P2.54mm_Vertical
Power: SW_Slide_SPDT_Angled_CK_OS102011MA1Q
R1: 20K; R_0805_2012Metric
R2: 10K; R_0805_2012Metric
R6, R7, R8, R9, R10, R11, R13, R14, R15: 4.7K; R_0805_2012Metric
R LED: R_0805_2012Metric
SMA: SMA_Amphenol_132289_EdgeMount
SW1, SW2, SW3: SW_Push; SW_Push_1P1T_XKB_TS-1187A
U4: SHT40-AD1B-R3; DFN4_SHT4x_SEN
U5: SGP41-D-R4; XDCR_SGP41-D-R4
U6: SCD41-D-R2; QFN20_SCD41-D-R2_SEN
XIAO ESP32: XIAO-ESP32-C5-DIP

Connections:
5V: FAN.2, MQ2.4, XIAO ESP32.14
+3V3: 0.96" OLED.2 (VCC_IN), C1.1, C2.1, C3.1, C4.1, C5.2, C6.1, C7.2, CCS811.1, HTU21D.1, J2.P4 (VDD), R6.1, R7.1, R8.2, R9.2, R10.2, R11.2, R13.2, R14.2, R15.2, SW3.2, U4.3 (VDD), U5.1 (VDD), U5.5 (VDDH), U6.7 (VDD), U6.19 (VDDH), XIAO ESP32.12
AO: MQ2.1, R2.2
BTN1: SW1.1, XIAO ESP32.7
BTN2: SW2.2, XIAO ESP32.8
BTSW1: BAT+.1, Power.2
D1: R LED.2, XIAO ESP32.2
GND: 0.96" OLED.1 (GND), BZ1.2 (-), BZ1#2.2, C1.2, C2.2, C3.2, C4.2, C5.1, C6.2, C7.1, CCS811.2, CCS811.5, FAN.1, HTU21D.3, IPEX.1, IPEX.2, J2.G1 (COVER_GND), J2.G2 (COVER_GND), J2.P6 (VSS), LED.2, Laser.1, MQ2.3, R1.1, SMA.2, SW1.2, SW2.1, U4.4 (VSS), U4.5 (EPAD), U5.2 (VSS), U5.4 (GND), U5.7 (GND), U6.6 (GND), U6.20 (GND), U6.21 (EPAD), XIAO ESP32.13
GPIO4: BZ1.1 (+), BZ1#2.1, XIAO ESP32.3
LASER: Laser.2, SW3.1
LED-R: LED.1, R LED.1
MQ2AO: R1.2, R2.1, XIAO ESP32.1
unnamed: J2.P8 (DAT1), R11.1
unnamed: J2.P1 (DAT2), R13.1
unnamed: J2.CD, R15.1
SCL: 0.96" OLED.3 (SCL), CCS811.3, HTU21D.4, R7.2, U4.2 (SCL), U5.6 (SCL), U6.9 (SCL), XIAO ESP32.6
SDA: 0.96" OLED.4 (SDA), CCS811.4, HTU21D.5, R6.2, U4.1 (SDA), U5.3 (SDA), U6.10 (SDA), XIAO ESP32.5
SDCLK: J2.P5 (CLK), R8.1, XIAO ESP32.9
SDCS: J2.P2 (CD/DAT3), R14.1, XIAO ESP32.4
SDSI: J2.P3 (CMD), R9.1, XIAO ESP32.11
SDSO: J2.P7 (DAT0), R10.1, XIAO ESP32.10
antenna: IPEX.3, SMA.1

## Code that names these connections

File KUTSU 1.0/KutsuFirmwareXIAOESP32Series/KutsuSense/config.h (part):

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// you swap modules.
//
//   pad   C3     C5     C6     S3     net on the Kutsu 1 board (rev 3)
//   D0    GPIO2  GPIO1  GPIO0  GPIO1  MQ2AO  (MQ-2 analog, via R2/R1 divider)
//   D1    GPIO3  GPIO0  GPIO1  GPIO2  D1     (warning LED, R15)
//   D2    GPIO4  GPIO25 GPIO2  GPIO3  GPIO4  (buzzer BZ1 +)
//   D3    GPIO5  GPIO7  GPIO21 GPIO4  SDCS
//   D4    GPIO6  GPIO23 GPIO22 GPIO5  SDA    (R13 + R4 pull-ups)
//   D5    GPIO7  GPIO24 GPIO23 GPIO6  SCL    (R14 + R3 pull-ups)
//   D6    GPIO21 GPIO11 GPIO16 GPIO43 BTN1   <- UART0 TX on every module
//   D7    GPIO20 GPIO12 GPIO17 GPIO44 BTN2   <- UART0 RX on every module
//   D8    GPIO8  GPIO8  GPIO19 GPIO7  SDCLK
//   D9    GPIO9  GPIO9  GPIO20 GPIO8  SDSO (MISO)
//   D10   GPIO10 GPIO10 GPIO18 GPIO9  SDSI (MOSI)
//
// Because D6/D7 are the UART0 pins on all four modules, "USB CDC On Boot" MUST
// be Enabled (the sketch refuses to compile otherwise) so Serial uses USB.
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#define PIN_SCL      D5        // net SCL
#define I2C_HZ       100000    // CCS811 clock-stretches; keep 100 kHz

#define PIN_SD_SCK   D8        // net SDCLK (J1 CLK)
#define PIN_SD_MISO  D9        // net SDSO  (J1 DAT0)
#define PIN_SD_MOSI  D10       // net SDSI  (J1 CMD)
#define PIN_SD_CS    D3        // net SDCS  (J1 CD/DAT3)
#define SD_HZ        1000000

#define PIN_BUTTON   D6        // net BTN1 (SW2 on rev 3)
#define PIN_BUTTON2  D7        // net BTN2 (SW3 on rev 3, reserved)
#define PIN_BUZZER   D2        // net GPIO4 (BZ1 +)
#define PIN_LED      D1        // warning LED (D1 -> R15 -> LED -> GND)
#define LED_ACTIVE_HIGH 1      // 1 = drive HIGH to light the LED

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
// ---- XIAO ESP32-C6 RF switch (module-internal GPIOs; C6 only) ---------------
// The board variant already powers the switch (GPIO3 LOW) and selects the
// on-board antenna (GPIO14 LOW) before setup(). Set 1 for the enclosure's
// external whip antenna on the u.FL connector.
#define RF_SWITCH_EN_GPIO   3
#define RF_ANT_SEL_GPIO     14
#define RF_USE_EXTERNAL_ANT 0     // 0 = on-board ceramic antenna, 1 = external u.FL

// ---- I2C addresses (probed at boot; first match wins) -----------------------
#define ADDR_SSD1306     0x3C   // DS1 panel: D/C# (SA0) tied to GND -> 0x3C
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

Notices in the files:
README.md:
License: Apache-2.0
